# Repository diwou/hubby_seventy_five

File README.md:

# HUB75 NTP Flip Clock

Eine animierte Flip-Clock auf einem oder zwei 64×32 HUB75 LED-Matrix-Displays, betrieben von einem ESP32-S3.
Zeigt Uhrzeit (NTP-synchronisiert), Datum und aktuelle Wetterdaten an. Vollständig über ein Browser-Webinterface konfigurierbar — kein Neu-Flashen notwendig.

**Aktuelle Version:** 1.6.2

**Repository:** https://codeberg.org/diwou/hubby_seventy_five

**Lizenz:** CC BY-NC-SA 4.0, siehe [LICENSE](LICENSE)

**Browser-Installer:** `index.html` bzw. `install.html` nutzen automatisch `Firmware/latest/manifest.json`

<p>
  
</p>

---

## Inhalt

1. [Features](#features)
2. [Hardware](#hardware)
3. [Verkabelung / GPIO](#verkabelung--gpio)
4. [Software-Setup (PlatformIO)](#software-setup-platformio)
5. [Manuelles Update Ohne IDE](#manuelles-update-ohne-ide)
6. [Erstbetrieb](#erstbetrieb)
7. [Webinterface](#webinterface)
8. [Konfigurationsreferenz](#konfigurationsreferenz)
9. [Display-Layout](#display-layout)
10. [Animationsmodi](#animationsmodi)
11. [Sekundenanzeige-Modi](#sekundenanzeige-modi)
12. [REST-API](#rest-api)
13. [Architektur / Code-Struktur](#architektur--code-struktur)
14. [Changelog](#changelog)
15. [Lizenz](#lizenz)

---

## Features

- **Animierte Flip-Clock** — Ziffernwechsel mit Slide-Up- oder Cross-Dissolve-Animation
- **NTP-Zeitsynchronisation** — bis zu 3 konfigurierbare NTP-Server, automatischer Re-Sync
- **Wetteranzeige** — aktuelles Wetter + 3-Tage-Vorhersage via OpenWeatherMap API
- **Captive Portal** — bei fehlendem WLAN öffnet sich automatisch ein Konfigurations-Hotspot
- **Webinterface** — vollständige Konfiguration im Browser unter `http://hub75clock.local`
- **Umschaltbares Panel-Layout** — 1× HUB75 oder 2× HUB75 nebeneinander, mit vorbereiteter Mapping-Struktur für spätere 2×2-Layouts
- **OTA-Updates** — Firmware-Update über WLAN (ArduinoOTA)
- **Konfigurierbare Farben** — 8 Farbwähler für alle Display-Elemente
- **Mehrere Anzeigemodi** — 12h/24h, 4 Datumsformate, 4 Sekundenanzeige-Varianten
- **Zweisprachig** — Wochentage und Wetterbeschreibungen auf Deutsch oder Englisch
- **Double-Buffering** — kein Flackern oder Tearing

---

## Hardware

| Komponente | Beschreibung |
|---|---|
| **Mikrocontroller** | Freenove ESP32-S3 WROOM N16R8 (16 MB Flash, 8 MB PSRAM) |
| **Display** | 64×32 HUB75 RGB LED-Matrix, 1 oder 2 Panels nebeneinander |
| **Pegelwandler** | 74HCT245 (3,3 V → 5 V für HUB75-Signale) |

### KiCad / Platine

Die Platine liegt unter [`kicad/`](kicad/). Die bearbeitbaren KiCad-Quellen liegen in [`kicad/source/`](kicad/source/), die auslieferbaren Fertigungsdaten für Revision `0.3` in [`kicad/fab/rev0.3/`](kicad/fab/rev0.3/). Dort findest Du Gerber, Bohrdaten, BOM, Positionsdateien und das komplette Fertigungspaket als ZIP.

---

## Verkabelung / GPIO

Das HUB75-Panel wird über einen **74HCT245**-Pegelwandler angeschlossen (3,3 V ESP32 → 5 V HUB75).

| HUB75-Signal | GPIO |
|---|---|
| R1 | 4 |
| G1 | 5 |
| B1 | 6 |
| R2 | 7 |
| G2 | 8 |
| B2 | 9 |
| A | 10 |
| B | 11 |
| C | 12 |
| D | 13 |
| E | –1 (ungenutzt, 32-Zeilen-Panel) |
| CLK | 14 |
| LAT | 17 |
| OE | 18 |

> **Hinweis:** Pin E wird nur bei 64-Zeilen-Panels benötigt. Bei diesem 32-Zeilen-Panel bleibt er unverbunden (–1).

---

## Software-Setup (PlatformIO)

### Voraussetzungen

- [PlatformIO](https://platformio.org/) (CLI oder VSCode-Extension)
- USB-Kabel oder WLAN (für OTA nach Erstflash)

### Befehle

```bash
# Firmware bauen
pio run

# Firmware flashen (USB, /dev/ttyACM0)
pio run --target upload

# Firmware flashen (OTA, wenn schon eingerichtet)
# → upload_port in platformio.ini auf IP-Adresse setzen
pio run --target upload

# Serieller Monitor (115200 Baud)
pio device monitor

# Build-Verzeichnis leeren
pio run --target clean
```

Nach jedem erfolgreichen `pio run` exportiert PlatformIO die flashbaren Dateien automatisch nach:

```text
Firmware/<Version>/
Firmware/latest/
```

Dort liegen jeweils:
- `bootloader.bin`
- `partitions.bin`
- `boot_app0.bin`
- `firmware.bin`
- `manifest.json`

Damit hast Du pro Version direkt einen vorbereiteten Satz fuer Browser-Flasher oder Release-Downloads.

Fuer einen einfachen USB-Erstflash ohne IDE gibt es ausserdem die Dateien `index.html` und `install.html`.
`index.html` dient als Startseite fuer statisches Hosting wie Codeberg Pages und leitet auf den eigentlichen Installer weiter. `install.html` verwendet automatisch den neuesten Export aus `Firmware/latest/manifest.json`.

> **OTA vs. USB:** In `platformio.ini` ist standardmäßig OTA (`upload_protocol = espota`) konfiguriert.
> Für USB-Flash die Zeile `upload_protocol = espota` auskommentieren und `upload_port = /dev/ttyACM0` einkommentieren.

### Repository klonen

```bash
git clone ssh://git@codeberg.org/diwou/hubby_seventy_five.git
cd hubby_seventy_five
```

### Verwendete Bibliotheken

| Bibliothek | Version | Zweck |
|---|---|---|
| `mrfaptastic/ESP32 HUB75 LED MATRIX PANEL DMA Display` | ^3.0.14 | DMA-Display-Treiber |
| `adafruit/Adafruit GFX Library` | ^1.12.5 | Text, Formen, Farben |
| `mathieucarbou/ESPAsyncWebServer` | ^3.3.0 | Asynchroner Webserver |
| `mathieucarbou/AsyncTCP` | ^3.2.0 | Async-TCP-Unterbau |
| `bblanchon/ArduinoJson` | ^7.2.0 | JSON (Config + OWM-API) |

---

## Manuelles Update Ohne IDE

Wer weder die Arduino IDE noch VS Code mit PlatformIO nutzen moechte, kann die Dateien aus `Firmware/latest/` oder aus einer festen Version wie `Firmware/1.6.2/` direkt mit `esptool` flashen.

Die vier relevanten Flash-Offets sind:

```text
0x0000   bootloader.bin
0x8000   partitions.bin
0xE000   boot_app0.bin
0x10000  firmware.bin
```

Vorbereitung:
- Geraet per USB anschliessen
- Seriellen Port ermitteln
- Falls noetig `esptool` installieren: `pip install esptool`

### Linux

USB-Port haeufig: `/dev/ttyACM0` oder `/dev/ttyUSB0`

```bash
esptool.py --chip esp32s3 --port /dev/ttyACM0 --baud 921600 --before default_reset --after hard_reset write_flash -z \
  0x0000 Firmware/latest/bootloader.bin \
  0x8000 Firmware/latest/partitions.bin \
  0xE000 Firmware/latest/boot_app0.bin \
  0x10000 Firmware/latest/firmware.bin
```

### macOS

USB-Port haeufig: `/dev/cu.usbmodem...` oder `/dev/cu.usbserial...`

```bash
esptool.py --chip esp32s3 --port /dev/cu.usbmodemXXXX --baud 921600 --before default_reset --after hard_reset write_flash -z \
  0x0000 Firmware/latest/bootloader.bin \
  0x8000 Firmware/latest/partitions.bin \
  0xE000 Firmware/latest/boot_app0.bin \
  0x10000 Firmware/latest/firmware.bin
```

### Windows

USB-Port haeufig: `COM3`, `COM4`, `COM5`, ...

```powershell
esptool.py --chip esp32s3 --port COM4 --baud 921600 --before default_reset --after hard_reset write_flash -z `
  0x0000 Firmware/latest/bootloader.bin `
  0x8000 Firmware/latest/partitions.bin `
  0xE000 Firmware/latest/boot_app0.bin `
  0x10000 Firmware/latest/firmware.bin
```

Hinweise:
- Wenn `esptool.py` nicht gefunden wird, klappt oft auch `python -m esptool`.
- Bei einer festen Release-Version statt `Firmware/latest/` einfach z. B. `Firmware/1.6.2/` verwenden.
- Wer gar nichts lokal installieren moechte, kann alternativ weiter den Browser-Installer nutzen.
- Der Browser-Installer ist bereits auf dem aktuellen Stand: `Firmware/latest/manifest.json` zeigt derzeit auf Version `1.6.2`.

---

## Erstbetrieb

1. **Firmware flashen** (USB):
   ```bash
   # upload_port in platformio.ini auf /dev/ttyACM0 setzen
   pio run --target upload
   ```

2. **Mit dem Hotspot verbinden:**
   Das Display zeigt `AP-Modus` und den SSID-Namen `HUB75CLOCK-XXXX`.
   Mit diesem WLAN verbinden — das Captive Portal öffnet sich automatisch.
   (Falls nicht: Browser öffnen und `http://192.168.4.1` aufrufen.)

3. **WLAN konfigurieren:**
   Im Tab **WLAN** → SSID und Passwort eingeben → **Speichern & Neustart**.

4. **Nach dem Neustart:**
   Das Display scrollt kurz die IP-Adresse und `hub75clock.local`.
   Das Webinterface ist erreichbar unter:
   - `http://hub75clock.local` (mDNS, empfohlen)
   - `http://<IP-Adresse>` (IP aus dem Router ablesen oder Serial Monitor)

5. **OpenWeatherMap einrichten** (optional, für Wetteranzeige):
   - Kostenloser API-Key: [openweathermap.org](https://openweathermap.org/api)
   - Im Tab **Wetter** → API-Key + Stadtname eingeben → **Speichern**

6. **Zeitzone prüfen:**
   Im Tab **NTP** → Zeitzone als POSIX-String einstellen.
   Standard: `CET-1CEST,M3.5.0,M10.5.0/3` (Europa/Berlin mit Sommerzeit)

---

## Webinterface

Das Webinterface ist in sechs Tabs gegliedert:

Geschuetzte API-Aktionen verwenden HTTP Basic Auth. Standardzugang nach einem
Factory Reset: Benutzer `admin`, Passwort `hub75clock`. Das Web-Passwort sollte
im Tab **WLAN** geaendert werden.

### Status
Zeigt Systeminformationen in Echtzeit (Auto-Refresh jede Sekunde):
- Firmware-Version, IP-Adresse, WLAN-SSID und Signalstärke (RSSI)
- Uptime, aktuelle Uhrzeit
- NTP-Synchronisationsstatus und aktiver NTP-Server
- Wetter-Standort, aktuelle Temperatur und Wetterbedingung
- Nächste geplante NTP- und Wetter-Aktualisierung
- Freier Heap-Speicher

Schaltflächen: **Aktualisieren**, **Neustart**, **Factory Reset**

### WLAN
- SSID und Passwort für das Heimnetz
- AP-Passwort (leer = offener Hotspot ohne Passwort, sonst mindestens 8 Zeichen)
- Web-Passwort fuer HTTP Basic Auth (Benutzer `admin`, mindestens 8 Zeichen)
- WLAN-Verbindungs-Timeout (Standard: 30 s)

### NTP
- Bis zu 3 NTP-Server (Standard: `pool.ntp.org`, `time.google.com`, `time.cloudflare.com`)
- Sync-Intervall (Standard: 15 min)
- Zeitzone: Freitext-POSIX-String oder Auswahl aus Vorlagen (Berlin, London, Athen, UTC, USA)

### Wetter
- OpenWeatherMap API-Key
- Standort: Stadtname mit Geo-Suche **oder** GPS-Koordinaten (Breitengrad / Längengrad)
- Temperatureinheit: Celsius oder Fahrenheit
- Abruf-Intervall (Standard: 30 min)

### Anzeige
- Helligkeit (0–255)
- HUB75-Layout: `1x HUB75 (64x32)` oder `2x HUB75 nebeneinander (128x32)`
- Sprache: Deutsch / Englisch (Wochentage, Wetterbeschreibungen)
- Zeitformat: 24h oder 12h (AM/PM-Indikator)
- Datumsformat: 4 Varianten (siehe [Konfigurationsreferenz](#konfigurationsreferenz))
- Animations-Modus: Slide-Up oder Cross-Dissolve
- Sekundenanzeige: Bar / Wanderpunkt / Dots / HH:MM:SS
- Wetter-Wechselintervall (untere Zeile, Standard: 6 s)
- Scroll-Geschwindigkeit (30 = schnell, 200 = langsam, Standard: 80 ms/Pixel)
- **Farben:** 8 Farbwähler für alle Display-Elemente

Änderungen am HUB75-Layout werden erst nach einem Neustart aktiv, weil die Matrix-DMA-Konfiguration beim Booten initialisiert wird.

### OTA
- OTA-Updates aktivieren / deaktivieren
- Optionales OTA-Passwort
- OTA-Hostname: `hub75clock.local`, Port: 8266

---

## Konfigurationsreferenz

Alle Einstellungen werden in `/cfg.json` auf dem LittleFS-Dateisystem gespeichert.

### WLAN

| Parameter | Standard | Beschreibung |
|---|---|---|
| `sta_ssid` | `""` | SSID des Heimnetzwerks |
| `sta_pass` | `""` | WLAN-Passwort |
| `ap_password` | `""` | Passwort für den Konfigurationshotspot (leer = offen) |
| `web_password` | `hub75clock` | Passwort fuer das Webinterface, Benutzer `admin` |
| `wifi_timeout_sec` | `30` | Verbindungs-Timeout in Sekunden |

### NTP

| Parameter | Standard | Beschreibung |
|---|---|---|
| `ntp1` | `pool.ntp.org` | Primärer NTP-Server |
| `ntp2` | `time.google.com` | Sekundärer NTP-Server |
| `ntp3` | `time.cloudflare.com` | Tertiärer NTP-Server |
| `ntp_interval_min` | `15` | Re-Sync-Intervall in Minuten |
| `tz` | `CET-1CEST,M3.5.0,M10.5.0/3` | Zeitzone als POSIX-String |

**Zeitzone-Beispiele:**

| Zeitzone | POSIX-String |
|---|---|
| Europa/Berlin (mit Sommerzeit) | `CET-1CEST,M3.5.0,M10.5.0/3` |
| Europa/London | `GMT0BST,M3.5.0/1,M10.5.0` |
| UTC | `UTC0` |
| USA/New York | `EST5EDT,M3.2.0,M11.1.0` |
| USA/Los Angeles | `PST8PDT,M3.2.0,M11.1.0` |

### Wetter

| Parameter | Standard | Beschreibung |
|---|---|---|
| `owm_apikey` | `""` | OpenWeatherMap API-Key |
| `owm_city` | `""` | Stadtname (z. B. `Berlin`) |
| `owm_lat` / `owm_lon` | `0.0` | GPS-Koordinaten (nur wenn `owm_use_coords=true`) |
| `owm_use_coords` | `false` | `true` = Koordinaten, `false` = Stadtname |
| `owm_unit` | `0` | `0` = Celsius, `1` = Fahrenheit |
| `owm_interval_min` | `30` | Abruf-Intervall in Minuten |

### Anzeige

| Parameter | Standard | Beschreibung |
|---|---|---|
| `brightness` | `90` | Display-Helligkeit (0–255) |
| `lang` | `"de"` | Sprache: `"de"` oder `"en"` |
| `time_12h` | `0` | `0` = 24h, `1` = 12h (AM/PM) |
| `date_format` | `0` | Datumsformat (0–3, siehe unten) |
| `anim_mode` | `0` | `0` = Slide-Up, `1` = Cross-Dissolve |
| `seconds_mode` | `0` | `0` = Bar, `1` = Pulse, `2` = Dots, `3` = HH:MM:SS |
| `display_panel_cols` | `2` | Aktuell unterstützt: `1` = ein Panel, `2` = zwei Panels nebeneinander |
| `display_panel_rows` | `1` | Vorbereitung für späteres 2×2-Layout; derzeit im Webinterface fest auf `1` |
| `display_panel_map` | `0` | Vorbereitung für Mapping-Modi: `0` = linear, `1` = ZigZag/Serpentine; derzeit noch nicht im Webinterface auswählbar |
| `bottom_cycle_sec` | `6` | Wechselintervall der Wetterzeile in Sekunden |
| `scroll_speed_ms` | `40` | Scroll-Geschwindigkeit in ms pro Pixel (30–200) |

**Datumsformate:**

| Wert | Beispiel | Beschreibung |
|---|---|---|
| `0` | `Mo 17.03.26` | Wochentag + TT.MM.JJ (Standard) |
| `1` | `Mo 17.03` | Wochentag + TT.MM (ohne Jahr) |
| `2` | `17.03.2026` | TT.MM.JJJJ (lang, ohne Wochentag) |
| `3` | `03/17/26` | MM/TT/JJ (US-Format) |

### Farben

Alle Farben im Format `#RRGGBB`:

| Parameter | Standard | Element |
|---|---|---|
| `color_digit` | `#FFC832` | Uhrziffern (Gold/Amber) |
| `color_date` | `#64A0FF` | Datumtext (Blau) |
| `color_temp` | `#FF8C28` | Temperaturanzeige (Orange) |
| `color_warn` | `#FFDC00` | Wochentag / Warnmeldungen (Gelb) |
| `color_info` | `#A0A0A0` | Info-Texte (Grau) |
| `color_sec` | `#C88C14` | Sekunden-Balken (Dunkelamber) |
| `color_sec5` | `#00DC46` | 5s-Marke im Sekundenbalken (Grün) |
| `color_sec10` | `#50DCFF` | 10s-Marke im Sekundenbalken (Cyan) |

### OTA

| Parameter | Standard | Beschreibung |
|---|---|---|
| `ota_enabled` | `true` | OTA-Updates aktiviert |
| `ota_password` | `""` | OTA-Passwort (leer = kein Passwort) |

---

## Display-Layout

Die Firmware kann aktuell mit einem oder zwei 64×32-HUB75-Panels betrieben werden:

| Einstellung | Virtuelle Größe | Verhalten |
|---|---:|---|
| `1x HUB75` | 64×32 px | Uhr, Datum und Wetter laufen wie im klassischen Ein-Panel-Layout auf einem Panel |
| `2x HUB75 nebeneinander` | 128×32 px | Uhr bleibt links, Datum nutzt das rechte Panel, die Wetterzeile scrollt über die volle Breite |

Die Konfiguration speichert bereits `display_panel_cols`, `display_panel_rows` und `display_panel_map`. Dadurch ist die Struktur für ein späteres 2×2-Layout vorbereitet. Für 2×2 muss zusätzlich das physische Panel-Mapping implementiert werden, z. B. linear oder ZigZag/Serpentine passend zur Verkabelung.

Bei `1x HUB75` verwendet `HH:MM:SS` bewusst das kompakte Ein-Panel-Layout aus Version `1.5.4`, damit die sechs Ziffern auf 64×32 px nicht zu groß dargestellt werden. Bei `2x HUB75 nebeneinander` bleibt das größere aktuelle Layout aktiv.

Das 64×32-Basislayout ist in vier Bereiche aufgeteilt:

```
┌─────────────────────────────────────────────────────────────────┐ y=0
│                                                                 │
│   Uhrzeit: HH:MM (10×14px Bitmap-Ziffern, Gold/Amber)          │ y=0..13
│                                                                 │
├─────────────────────────────────────────────────────────────────┤ y=14
│   Sekundenanzeige (2px, Mode 0–2) — entfällt bei Mode 3        │ y=14..15
├─────────────────────────────────────────────────────────────────┤ y=16
│   Gap (1px)                                                     │ y=16
├─────────────────────────────────────────────────────────────────┤ y=17
│   Datum: z. B. "Mo 17.03.26"  /  Temperatur (rechtsbündig)     │ y=17..23
├─────────────────────────────────────────────────────────────────┤ y=24
│   Gap (1px)                                                     │ y=24
├─────────────────────────────────────────────────────────────────┤ y=25
│   Wetter (rotierend): Aktuell → Di-Forecast → Mi → Do          │ y=25..31
└─────────────────────────────────────────────────────────────────┘ y=31
```

### Ziffern-Positionen HH:MM (Mode 0–2)

```
H1=7  H2=19  [:]=31  M1=35  M2=47
```
(Kolon: 2×2-Pixel-Punkte bei y=3 und y=9)

### Ziffern-Positionen HH:MM:SS (Mode 3)

```
H1=2  H2=11  [C1]=20..21  M1=23  M2=32  [C2]=41..42  S1=44  S2=53
```
(9px-Ziffern, 2×2-Pixel-Kolons)

### Wetterzeile (rotierend, Wechsel alle `bottom_cycle_sec` Sekunden)

| Modus | Inhalt | Beispiel |
|---|---|---|
| 0 | Aktuelles Wetter scrollend | `+12.4C  Leicht bew.` |
| 1 | Vorhersage +1 Tag statisch | `Di +15/-3` |
| 2 | Vorhersage +2 Tage statisch | `Mi +12/-1` |
| 3 | Vorhersage +3 Tage statisch | `Do +8/-5` |

---

## Animationsmodi

### Slide-Up (`anim_mode = 0`)
- 14 Frames à 15 ms = ~210 ms Gesamtdauer
- Phase 1 (Frame 0–6): Alte Ziffer gleitet nach oben aus dem Slot heraus
- Phase 2 (Frame 7–13): Neue Ziffer gleitet von unten in den Slot hinein

### Cross-Dissolve (`anim_mode = 1`)
- 14 Frames à 18 ms = ~252 ms Gesamtdauer
- Phase 1 (Frame 0–6): Alte Ziffer blendet von voll → schwarz aus (7 Helligkeitsstufen)
- Phase 2 (Frame 7–13): Neue Ziffer blendet von schwarz → voll ein

### Kolon-Animation
- Synchron zum Sekundenwechsel: Cross-Dissolve-Puls (14 Frames à 18 ms)
- Der Kolon bleibt dauerhaft hell und pulsiert kurz zum Sekundenwechsel
- Außerhalb der Animation: statisch in Ziffernfarbe

---

## Sekundenanzeige-Modi

| Modus | Beschreibung |
|---|---|
| `0` — Bar | Balken füllt sich von links; 5s-Marken grün, 10s-Marken cyan |
| `1` — Pulse | Ein Leuchtpunkt wandert mit kurzem Schweif von links nach rechts |
| `2` — Dots | 60 Einzelpunkte; vergangene Sekunden leuchten, zukünftige sind gedimmt |
| `3` — HH:MM:SS | Kein Sekundenbalken — Sekunden erscheinen direkt in der Uhrzeitzeile |

---

## REST-API

Das Webinterface kommuniziert über eine interne JSON-API. Alle Endpunkte sind unter der IP-Adresse des Geräts erreichbar und per HTTP Basic Auth geschützt (`admin` + Web-Passwort).

| Methode | Endpunkt | Beschreibung |
|---|---|---|
| `GET` | `/api/config` | Konfigurationswerte als JSON abrufen; gespeicherte Passwoerter/API-Keys werden nicht ausgeliefert |
| `POST` | `/api/config` | Konfiguration aktualisieren (JSON-Body) |
| `GET` | `/api/status` | Systemstatus (Firmware, IP, WLAN, NTP, Wetter) |
| `GET` | `/api/geocode?q={Stadt}` | Ortsuche via OWM Geocoding API (bis zu 5 Treffer) |
| `GET` | `/api/restart` | Gerät neu starten |
| `GET` | `/api/reset` | Factory Reset (alle Einstellungen löschen + Neustart) |

### Beispiel: Konfiguration per curl ändern

```bash
# Helligkeit auf 150 setzen
curl -X POST http://hub75clock.local/api/config \
  -u admin:<web-passwort> \
  -H "Content-Type: application/json" \
  -d '{"brightness": 150}'

# Auf ein einzelnes HUB75-Panel umstellen; Neustart danach erforderlich
curl -X POST http://hub75clock.local/api/config \
  -u admin:<web-passwort> \
  -H "Content-Type: application/json" \
  -d '{"display_panel_cols": 1, "display_panel_rows": 1}'

# Aktuellen Status abrufen
curl -u admin:<web-passwort> http://hub75clock.local/api/status
```

---

## Architektur / Code-Struktur

```
src/
├── main.cpp       — Setup, Loop, WiFi-State-Machine, NTP-Sync, Wetter-Timer
├── config.h       — Config-Struct, LittleFS-Persistenz (configLoad/Save/Reset)
├── display.h      — HUB75-Initialisierung, Bitmap-Font, Flip-Animationen, Display-Update
├── weather.h      — OpenWeatherMap HTTP-Fetch, Wetter-Datenstruktur, Geocoding
└── webserver.h    — AsyncWebServer, REST-API, Captive-Portal, OTA-Setup, HTML/CSS/JS
include/
├── config.h       — `APP_VERSION_BASE` als sichtbare Basisversion
└── version_generated.h — beim Build erzeugter Firmware-String mit Git-Hash
```

### Wichtige Abhängigkeiten

```
main.cpp
  ├── config.h      (cfg, configLoad/Save/Reset)
  ├── display.h     (displayInit, displayUpdate, displayReset, ...)
  │     └── weather.h (WeatherData, forecastDayName)
  └── webserver.h   (webServerSetup, otaSetup, dnsServer)
        ├── extern MatrixPanel_I2S_DMA* dma_display  ← aus display.h
        └── extern bool ntpSynced                    ← aus main.cpp
```

> Alle `.h`-Dateien definieren globale Variablen direkt (kein ODR-Problem, da nur eine `.cpp`-Datei kompiliert wird).

### WiFi-State-Machine (`main.cpp`)

```
Start
  │
  ▼
wifiConnect() ──── Erfolg ──→ mDNS + NTP-Sync + WebServer + OTA + Wetter
  │
  Timeout
  │
  ▼
startAP() ──→ Hotspot "HUB75CLOCK-XXXX" + Captive-Portal + WebServer
                   (kein NTP, kein Wetter im AP-Modus)

Loop:
  WiFi verloren? ──→ alle 30 s Reconnect-Versuch
```

### Double-Buffering / Kein Flackern

Die HUB75-Bibliothek verwendet zwei DMA-Buffer. Jeder Frame wird in den Back-Buffer gezeichnet, dann mit `flipDMABuffer()` atomisch sichtbar gemacht. Statische Ziffern werden **nicht** gelöscht und neu gezeichnet — nur animierende oder als `dirty` markierte Slots werden aktualisiert.

Nach `ESP.restart()` werden RAM-Überreste durch `displayReset()` in `setup()` explizit gelöscht (verhindert Ghosting beim Soft-Reboot).

### Bitmap-Font

Die Ziffern basieren auf dem **Dottie 8×8-Font**, konvertiert in 10×14-Pixel-Bitmaps (PROGMEM). Jede Ziffer besteht aus 14 `uint16_t`-Werten (eine pro Zeile), wobei Bit 9 die linkeste Spalte repräsentiert.

---

## Changelog

Die vollständige Änderungshistorie steht in [CHANGELOG.md](CHANGELOG.md).

## Lizenz

Dieses Projekt steht unter der Lizenz **Creative Commons Attribution-NonCommercial-ShareAlike 4.0 International**.

Kurzform:
- Namensnennung erforderlich
- Keine kommerzielle Nutzung
- Bearbeitungen müssen unter derselben Lizenz weitergegeben werden

Details siehe [LICENSE](LICENSE) und:
https://creativecommons.org/licenses/by-nc-sa/4.0/

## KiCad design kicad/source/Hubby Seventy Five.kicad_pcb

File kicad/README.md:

# KiCad Hardware

Dieses Verzeichnis enthält die Platinenquellen und die exportierten Fertigungsdaten für den HUB75 Flip Clock.

## Struktur

- `source/` - bearbeitbare KiCad-Quellen für Revision `0.3`
- `fab/rev0.3/gerber/` - Gerber-, Bohr- und Layer-Exporte
- `fab/rev0.3/bom/` - BOM, Designatoren, Positionen und Netlist
- `fab/rev0.3/Hubby_Seventy_Five_0.3.zip` - komplettes Fertigungspaket für den Bestelldienstleister

## Kurz-BOM

_Abgeleitet aus `fab/rev0.3/bom/bom.csv` und per `scripts/render_kicad_bom_summary.py` generiert. Falls sich die Platine ändert, die Übersicht mit `python3 scripts/render_kicad_bom_summary.py --write-readme` neu schreiben._

<!-- BOM_SUMMARY_START -->

| Bereich | Bauteile | Bauform | Menge | Zweck |
|---|---|---|---:|---|
| MCU | `U5` ESP32-S3-WROOM-1 | ESP32-S3-WROOM-1 | 1 | Hauptprozessor, WLAN, Steuerlogik und PSRAM |
| Takt / Sensorik | `U2` DS3231S, `U4` BME680, `U21` VEML7700-TT | Bosch_LGA-8_3x3mm_P0.8mm_ClockwisePinNumbering, SOIC-16W_7.5x10.3mm_P1.27mm, XDCR_VEML7700-TT | 3 | Echtzeituhr, Temperatur/Luftfeuchte/Luftdruck, Helligkeit |
| Pegelwandler | `U3/U6` 74HCT245 | TSSOP-20_4.4x6.5mm_P0.65mm | 2 | 3,3 V auf 5 V fuer HUB75-Signale |
| Spannungsversorgung | `BT1` CR2032, `D1` SS14, `U1` TLV76133DCY | BatteryHolder_MYOUNG_BS-07-A1BJ001_CR2032, D_SMA, SOT-223-3_TabPin2 | 3 | 3,3-V-Regler, Schutzdiode, Backup-Batterie |
| Anschlüsse | `J1` USB_C_Receptacle_USB2.0_16P, `J2` PWR IN, `J3` HUB75 Connector | IDC-Header_2x08_P2.54mm_Vertical, JST_VH_B4P-VH_1x04_P3.96mm_Vertical, USB_C_Receptacle_GCT_USB4105-xx-A_16P_TopMnt_Horizontal | 3 | Strom, USB, Display-Anschluss |
| Taster | `SW1` Reset, `SW2` Factory Reset, `SW3` Boot | SW_PUSH_6mm | 3 | Bedienung und Flash-Modus |
| Widerstände | `R1/R2` 5k1, `R3/R4/R5` 4k7, `R7` 1k, `R6/R8/R9/R10/R11` 10k, `R27` 10 | 0805 | 12 | Pullups, LED-/Signalbegrenzung, Schutz |
| Kondensatoren | `C1/C2/C3/C4/C7/C9/C10/C11/C13/C28` 100n, `C12` 1µ, `C5/C6/C8/C27` 10µ | 0805 | 15 | Abblockung und Pufferung |
| Anzeige / Status | `D2` PWR | 0805 | 1 | Power-LED |

<!-- BOM_SUMMARY_END -->

Hinweise:
- `H1` bis `H4` sind Montagebohrungen und tauchen deshalb nicht in der BOM-CSV auf.
- Die vollständige, exportierte Stückliste liegt zusätzlich als CSV unter `fab/rev0.3/bom/`.
- `U5` muss ein ESP32-S3-WROOM-1 mit PSRAM sein; das Projekt nutzt die PSRAM-Variante des Moduls.

## Hinweise

- Lokale KiCad-Backups bleiben per `.gitignore` ausgeschlossen.
- Die exportierten Fertigungsdaten sind bewusst im Repo, damit man sie ohne KiCad direkt bestellen oder prüfen kann.

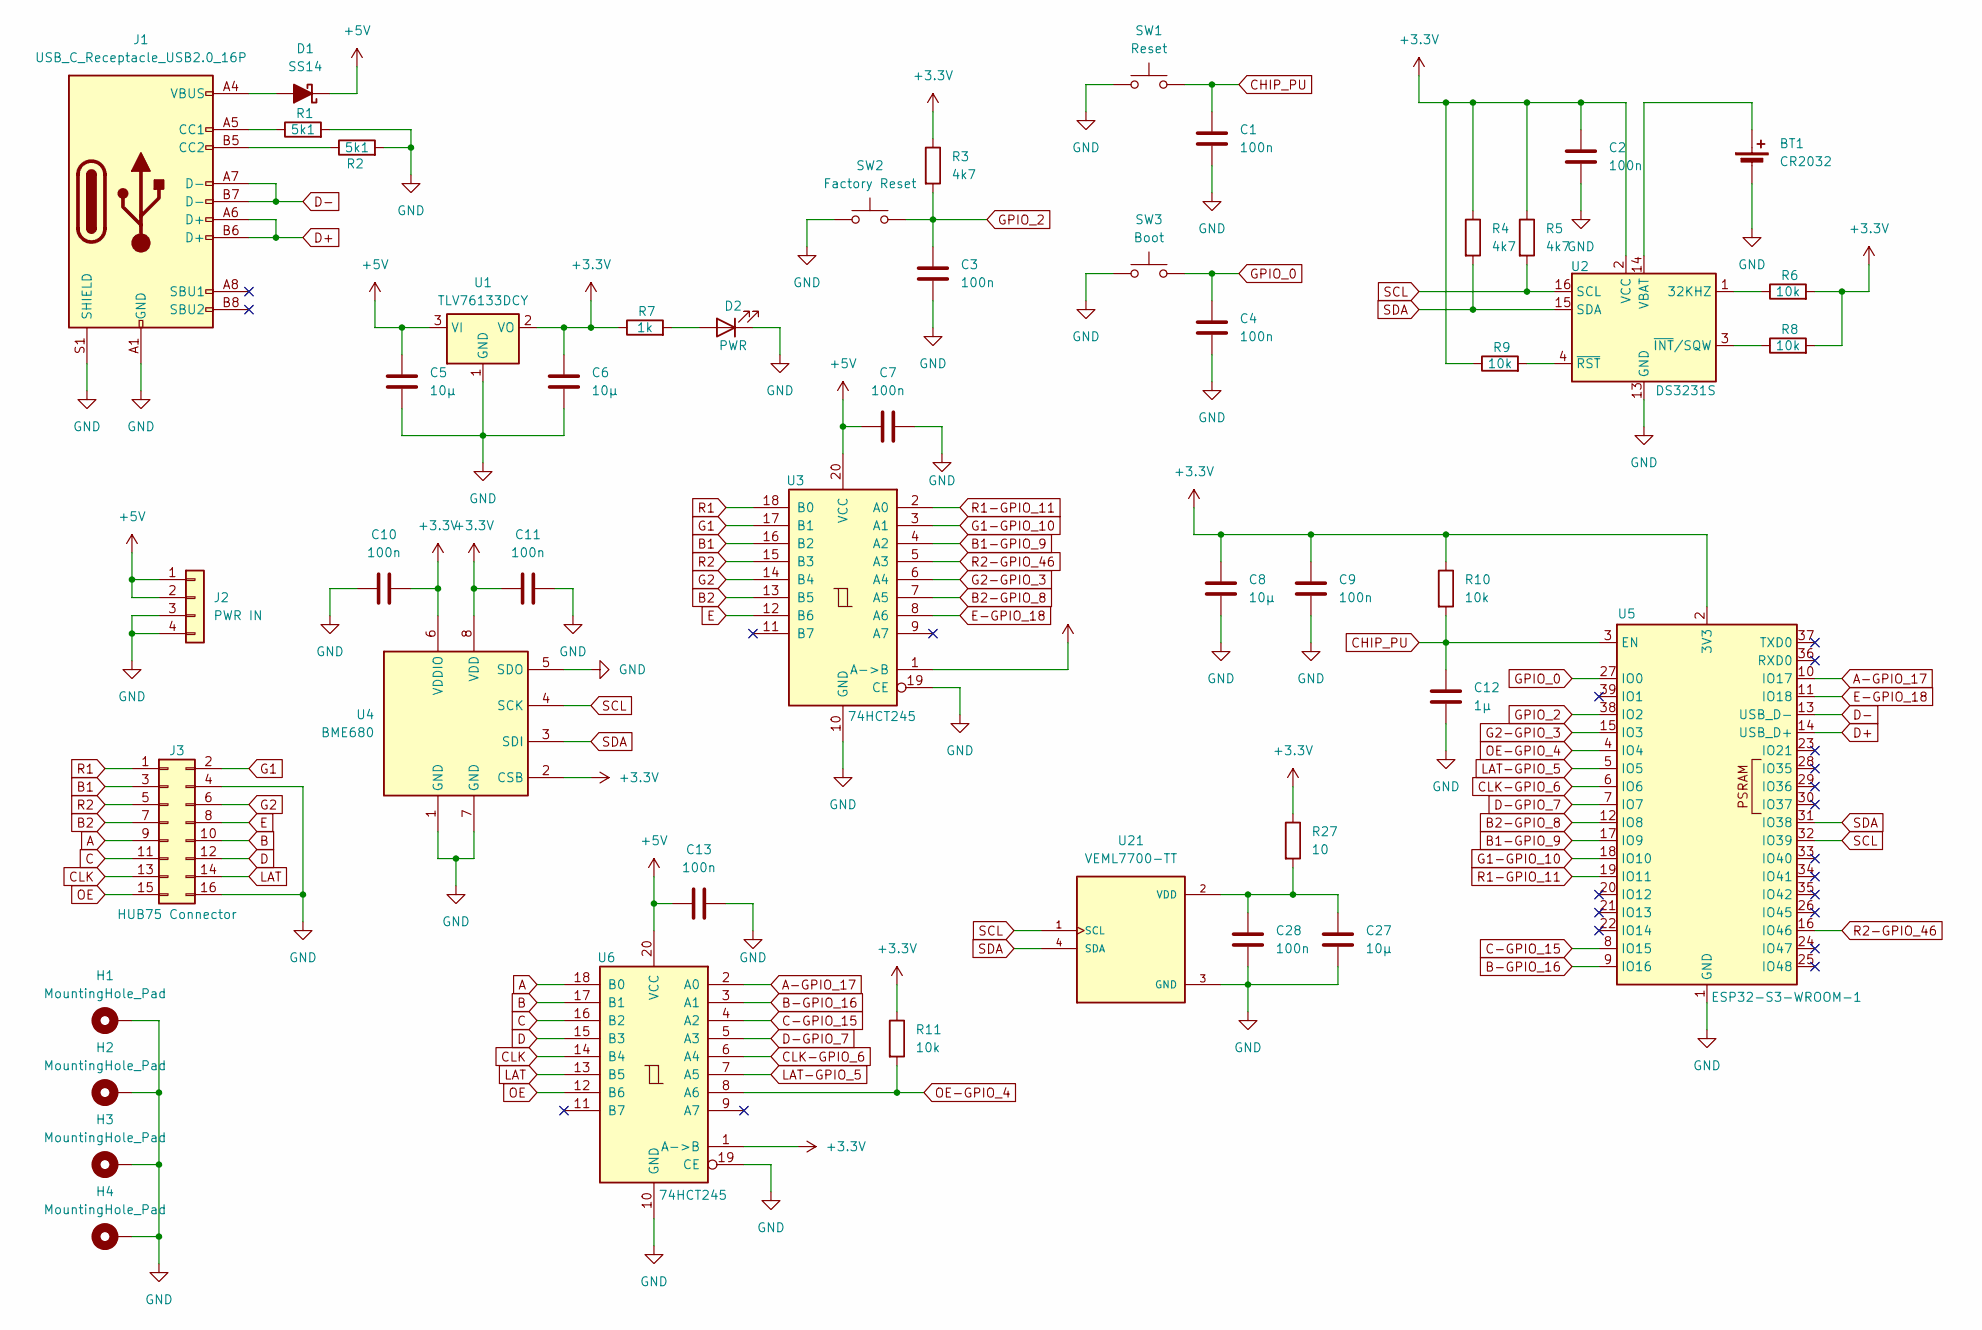
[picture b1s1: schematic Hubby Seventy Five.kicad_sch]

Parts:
BT1: CR2032; BatteryHolder_MYOUNG_BS-07-A1BJ001_CR2032
C1, C2, C3, C4, C7, C9, C10, C11, C13, C28: 100n; C_0805_2012Metric_Pad1.18x1.45mm_HandSolder
C5, C6, C8, C27: 10µ; C_0805_2012Metric_Pad1.18x1.45mm_HandSolder
C12: 1µ; C_0805_2012Metric_Pad1.18x1.45mm_HandSolder
D1: SS14; D_SMA
D2: PWR; LED_0805_2012Metric_Pad1.15x1.40mm_HandSolder
H1, H2, H3, H4: MountingHole_Pad; MountingHole_3.2mm_M3_DIN965_Pad
J1: USB_C_Receptacle_USB2.0_16P; USB_C_Receptacle_GCT_USB4105-xx-A_16P_TopMnt_Horizontal
J2: PWR IN; JST_VH_B4P-VH_1x04_P3.96mm_Vertical
J3: HUB75 Connector; IDC-Header_2x08_P2.54mm_Vertical
R1, R2: 5k1; R_0805_2012Metric_Pad1.20x1.40mm_HandSolder
R3, R4, R5: 4k7; R_0805_2012Metric_Pad1.20x1.40mm_HandSolder
R6, R8, R9, R10, R11: 10k; R_0805_2012Metric_Pad1.20x1.40mm_HandSolder
R7: 1k; R_0805_2012Metric_Pad1.20x1.40mm_HandSolder
R27: 10; R_0805_2012Metric_Pad1.20x1.40mm_HandSolder
SW1: Reset; SW_PUSH_6mm
SW2: Factory Reset; SW_PUSH_6mm
SW3: Boot; SW_PUSH_6mm
U1: TLV76133DCY; SOT-223-3_TabPin2
U2: DS3231S; SOIC-16W_7.5x10.3mm_P1.27mm
U3, U6: 74HCT245; TSSOP-20_4.4x6.5mm_P0.65mm
U4: BME680; Bosch_LGA-8_3x3mm_P0.8mm_ClockwisePinNumbering
U5: ESP32-S3-WROOM-1
U21: VEML7700-TT; XDCR_VEML7700-TT; PARTREV 1.6

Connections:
+3.3V: C2.1, C6.1, C8.1, C9.1, C10.2, C11.1, R3.1, R4.1, R5.1, R6.2, R7.1, R8.2, R9.1, R10.1, R11.1, R27.1, U1.2 (VO), U2.2 (VCC), U3.1 (A->B), U4.2 (CSB), U4.6 (VDDIO), U4.8 (VDD), U5.2 (3V3), U6.1 (A->B)
+5V: C5.1, C7.1, C13.1, D1.1 (K), J2.1, J2.2, U1.3 (VI), U3.20 (VCC), U6.20 (VCC)
A: J3.9, U6.18 (B0)
A-GPIO_17: U5.10 (IO17), U6.2 (A0)
B: J3.10, U6.17 (B1)
B1: J3.3, U3.16 (B2)
B1-GPIO_9: U3.4 (A2), U5.17 (IO9)
B2: J3.7, U3.13 (B5)
B2-GPIO_8: U3.7 (A5), U5.12 (IO8)
B-GPIO_16: U5.9 (IO16), U6.3 (A1)
C: J3.11, U6.16 (B2)
C-GPIO_15: U5.8 (IO15), U6.4 (A2)
CHIP_PU: C1.1, C12.1, R10.2, SW1.2, U5.3 (EN)
CLK: J3.13, U6.14 (B4)
CLK-GPIO_6: U5.6 (IO6), U6.6 (A4)
D: J3.12, U6.15 (B3)
D+: J1.A6 (D+), J1.B6 (D+), U5.14 (USB_D+)
D-: J1.A7 (D-), J1.B7 (D-), U5.13 (USB_D-)
D-GPIO_7: U5.7 (IO7), U6.5 (A3)
E: J3.8, U3.12 (B6)
E-GPIO_18: U3.8 (A6), U5.11 (IO18)
G1: J3.2, U3.17 (B1)
G1-GPIO_10: U3.3 (A1), U5.18 (IO10)
G2: J3.6, U3.14 (B4)
G2-GPIO_3: U3.6 (A4), U5.15 (IO3)
GND: BT1.2 (-), C1.2, C2.2, C3.2, C4.2, C5.2, C6.2, C7.2, C8.2, C9.2, C10.1, C11.2, C12.2, C13.2, C27.2, C28.2, D2.1 (K), H1.1, H2.1, H3.1, H4.1, J1.A1 (GND), J1.A12 (GND), J1.B1 (GND), J1.B12 (GND), J1.S1 (SHIELD), J2.3, J2.4, J3.4, J3.16, R1.2, R2.2, SW1.1, SW2.1, SW3.1, U1.1 (GND), U2.5 (GND), U2.6 (GND), U2.7 (GND), U2.8 (GND), U2.9 (GND), U2.10 (GND), U2.11 (GND), U2.12 (GND), U2.13 (GND), U3.10 (GND), U3.19 (CE), U4.1 (GND), U4.5 (SDO), U4.7 (GND), U5.1 (GND), U5.40 (GND), U5.41 (GND), U6.10 (GND), U6.19 (CE), U21.3 (GND)
GPIO_0: C4.1, SW3.2, U5.27 (IO0)
GPIO_2: C3.1, R3.2, SW2.2, U5.38 (IO2)
LAT: J3.14, U6.13 (B5)
LAT-GPIO_5: U5.5 (IO5), U6.7 (A5)
unnamed: BT1.1 (+), U2.14 (VBAT)
unnamed: D1.2 (A), J1.A4 (VBUS), J1.A9 (VBUS), J1.B4 (VBUS), J1.B9 (VBUS)
unnamed: D2.2 (A), R7.2
unnamed: J1.A5 (CC1), R1.1
unnamed: J1.B5 (CC2), R2.1
unnamed: R6.1, U2.1 (32KHZ)
unnamed: R8.1, U2.3 (~INT/SQW)
unnamed: R9.2, U2.4 (~RST)
unnamed: C27.1, C28.1, R27.2, U21.2 (VDD)
OE: J3.15, U6.12 (B6)
OE-GPIO_4: R11.2, U5.4 (IO4), U6.8 (A6)
R1: J3.1, U3.18 (B0)
R1-GPIO_11: U3.2 (A0), U5.19 (IO11)
R2: J3.5, U3.15 (B3)
R2-GPIO_46: U3.5 (A3), U5.16 (IO46)
SCL: R5.2, U2.16 (SCL), U4.4 (SCK), U5.32 (IO39), U21.1 (SCL)
SDA: R4.2, U2.15 (SDA), U4.3 (SDI), U5.31 (IO38), U21.4 (SDA)

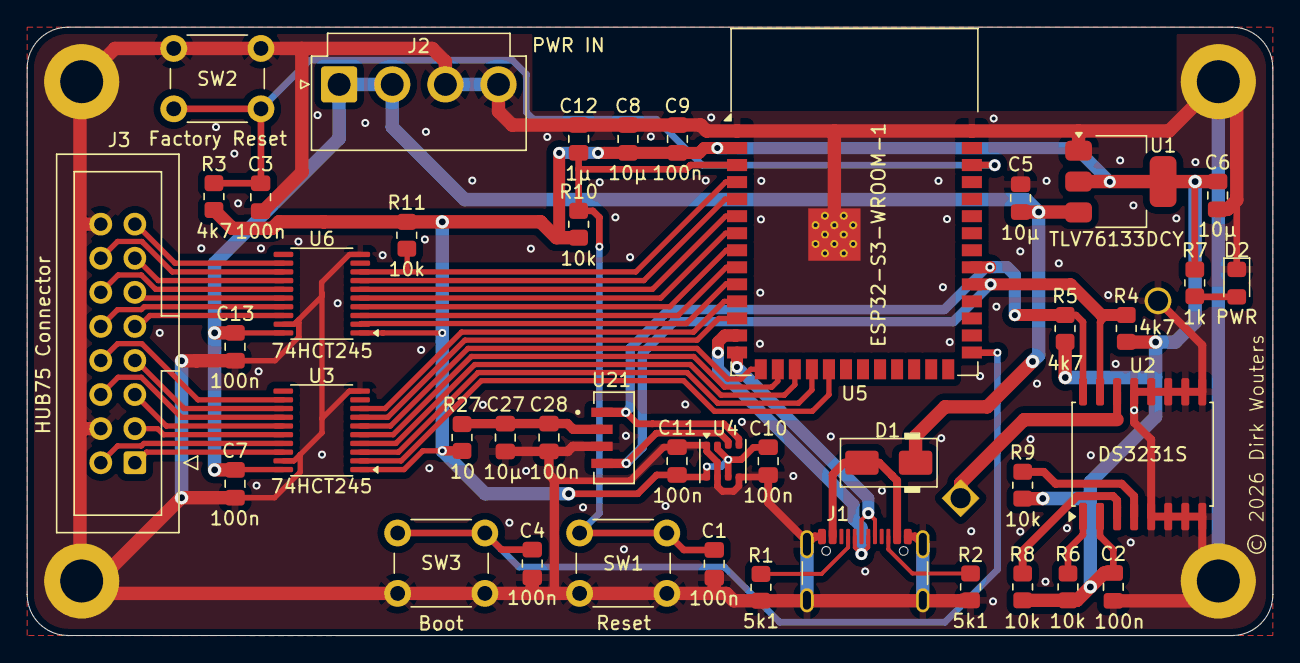
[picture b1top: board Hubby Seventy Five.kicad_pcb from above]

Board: 2 copper layers, 92.8 x 45.3 mm, 47 parts (1 on the bottom side), 47 nets.

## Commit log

2026-04-06 Initial public release v1.5.4
2026-04-06 Prepare installer page and firmware export
2026-04-06 Publish installer site
2026-04-06 Add index page for Codeberg Pages root
2026-04-06 Add index page for site root
2026-04-06 Trigger Codeberg Pages deploy
2026-04-06 Trigger Pages after making repo public
2026-04-06 Add installer button to README
2026-04-06 Sync README update to pages
2026-04-06 Keep firmware exports out of main branch
2026-04-06 Remove local-only helper scripts
2026-04-10 feat: expand dual-panel clock layout
2026-04-10 docs: record changelog codeberg reference
2026-04-10 fix: refine forecast spacing and enlarge clock
2026-04-10 docs: update changelog commit reference
2026-04-10 fix: use taller hhmm clock glyphs
2026-04-10 docs: reference codeberg ids per changelog entry
2026-04-10 fix: replace ineffective clock scaling with tall hhmm renderer
2026-04-10 docs: update changelog clock reference
2026-04-10 fix: enlarge hhmmss and clear mode switch artifacts
2026-04-10 docs: update changelog clock references
2026-04-10 fix: switch clock digits to bitmap-style scaling
2026-04-10 docs: update changelog font reference
2026-04-10 fix: finalize hhmmss layout and ota display lock
2026-04-10 docs: finalize changelog references for 1.6.0
2026-04-10 docs: record release id for 1.6.0
2026-04-10 docs: add manual update instructions without ide
2026-04-10 docs: note web ui firmware update for next version
2026-04-10 docs: finalize next-version changelog reference
2026-04-10 feat: add firmware upload via web interface
2026-04-10 docs: finalize changelog reference for web update
2026-04-10 fix: rebalance hhmmss colon spacing
2026-04-10 docs: finalize hhmmss colon changelog reference
2026-04-11 Add configurable HUB75 panel layout
2026-04-11 Prepare release 1.6.1
2026-04-11 chore: add reproducible cspell tooling
2026-04-11 docs: finalize cspell changelog reference
2026-04-19 Fix brief display blanks
2026-04-19 Add Codeberg reference to changelog
2026-04-19 Animate forecast transitions
2026-04-19 Document forecast transition animation
2026-04-19 Document forecast transition compile fix
2026-04-19 Fix forecast transition clipping
2026-04-19 Document forecast transition fix
2026-04-19 Keep forecast transition in weather area
2026-04-19 Document forecast transition adjustment
2026-04-19 Restore weather cycle transitions
2026-04-19 Document weather cycle restoration
2026-04-19 Restore weather cycle loop and clip transitions
2026-04-19 Document weather loop clipping fix
2026-04-19 Separate forecast fade phases
2026-04-19 Document separated forecast fade phases
2026-04-19 Keep forecast transitions out of clock area
2026-04-19 Document forecast clock area fix
2026-04-19 Redraw clock during forecast transition
2026-04-19 Document clock redraw during forecast transition
2026-04-19 Restore clock after forecast transition
2026-04-19 Add forecast transition clock restore reference
2026-04-19 Clip forecast transitions to weather area
2026-04-19 Document forecast clipping fix
2026-04-19 Publish 1.6.2 firmware
2026-04-19 Add watchdog and cspell updates
2026-04-19 Replace task WDT with heartbeat monitor
2026-04-19 Add KiCad source and fabrication exports
2026-04-19 Move KiCad fab zip to revision root
2026-04-19 Add human-readable KiCad BOM summary
2026-04-19 Fix watchdog and regenerate KiCad BOM summary
2026-04-19 Expose watchdog state in web UI
2026-04-19 Avoid blocking weather fetch during startup
2026-04-19 Reset WiFi stack on boot
2026-04-19 Unify firmware version source
2026-04-19 Reduce weather line flicker
2026-04-19 Soften weather scroll motion
2026-04-19 Smooth current weather scroll
2026-04-19 Stabilize weather scroll timing
2026-04-19 Load weather earlier and smooth scroll start
2026-04-19 Document weather startup refs
2026-04-19 Remove scroll overlay blending
2026-04-19 Document scroll overlay fix
2026-04-19 Reset weather scroll after forecast
2026-04-19 Document forecast scroll reset
2026-04-19 Smooth weather scrolling with supersampling
2026-04-19 Document supersampled weather scroll
2026-04-19 Avoid full weather band redraw
2026-04-19 Document reduced weather redraw flicker
2026-04-19 Batch weather band redraws by scanline
2026-04-19 Document scanline weather batching
2026-04-19 Enable PSRAM double buffering
2026-04-19 Document PSRAM double buffering
2026-04-19 Revert PSRAM double buffering
2026-04-19 Document PSRAM buffer rollback
2026-04-19 Revert weather scroll experiments
2026-04-19 Document weather rollback
2026-04-19 Smooth current weather scroll with supersampling
2026-04-19 Document smoother current weather scroll
2026-04-19 Try smoother weather scroll with fixed-point timing
2026-04-19 Reset weather scroll timing on restart
2026-04-19 Smooth current weather with 2x intermediate buffer
2026-04-19 Revert broken current weather 2x scroll experiment
2026-04-19 Reset weather scroll after forecast transition
2026-04-23 Document KiCad release workflow
2026-04-24 fix: HH:MM:SS auf 7px verbreitert
2026-04-24 docs: Changelog um Referenz ergänzt
2026-04-24 docs: Changelog-Reihenfolge korrigiert
2026-04-24 fix: HH:MM:SS im Legacy-Pfad verbreitert
2026-04-24 docs: Changelog auf Legacy-Fix referenziert
2026-04-24 fix: HH:MM:SS-Kantenbreite ohne Lochverlust
2026-04-24 docs: Changelog auf Loch-freien Fix referenziert
2026-04-24 fix: HH:MM:SS-Kantenform verfeinert
2026-04-24 docs: Changelog mit Kanten-Fix referenziert
2026-04-24 fix: HH:MM:SS mit eigenem 7px-Font
2026-04-24 docs: Changelog mit 7px-Font referenziert
2026-04-24 fix: HH:MM:SS auf volle Hoehe zurueck
2026-04-24 docs: Changelog auf volle Hoehe referenziert
2026-04-24 fix: HH:MM:SS-Font mit 2px-Strichen
2026-04-24 docs: Changelog mit 2px-Font referenziert
2026-04-24 revert: Font-Experimente zurücknehmen
2026-04-24 revert: heutige Font-Änderungen zurücknehmen
2026-04-24 fix: HH:MM:SS-Font auf 7x14-Tabelle umstellen
2026-04-24 docs: Changelog für HH:MM:SS-Font ergänzen
2026-04-24 fix: HH:MM:SS-Abstaende nach den Doppelpunkten korrigieren
2026-04-24 docs: Changelog fuer HH:MM:SS-Abstaende ergaenzen
2026-04-24 fix: OWM-Wetterpfad absichern
2026-04-24 docs: OWM-Fix im Changelog vermerken
2026-04-24 fix: HH:MM:SS-Ziffer 6 korrigieren
2026-04-24 docs: Changelog fuer Ziffer-6-Korrektur ergaenzen
2026-04-26 fix: sichere Web-API und Versionsquelle
2026-04-26 docs: Review-Fixes dokumentieren
2026-04-27 fix: Wetterabruf beim Boot entkoppeln
2026-04-27 docs: Boot-Fix im Changelog dokumentieren
2026-04-28 PlatformIO stabilisieren
2026-04-28 fix: stabilisiere Wetter-Scroll-Zeitbasis
2026-04-28 fix: glaette Wetter-Scroll per Subpixel-Blending
2026-04-28 fix: entferne unscharfes Wetter-Scroll-Blending
2026-04-28 fix: entlaste OTA und beschleunige Wetter-Scroll
2026-04-30 fix: stabilize cold boot startup
2026-05-11 feat: DS3231-Zeitquelle und RTC-Webfunktionen integrieren
2026-05-11 docs: Changelog-Referenzen auf Commit-ID aktualisieren
2026-05-11 feat: erweitere RTC/VEML status und kompakte 1x-forecast darstellung
2026-05-11 docs: aktualisiere changelog referenzen fuer rtc-veml und forecast-fix
2026-05-11 fix: stabilisiere autohelligkeit und strukturiere status-tabs
2026-05-11 docs: aktualisiere changelog-referenzen fuer autohelligkeit-fix
2026-05-11 feat: integriere bme680 wetterdaten und passe 1x-forecast spacing an
2026-05-11 docs: aktualisiere changelog-referenzen fuer bme680 und forecast-spacing
2026-05-11 fix: entkopple bme680 messung vom render-loop
2026-05-11 docs: aktualisiere changelog-referenz fuer bme680 async-fix
2026-05-11 fix: stoppe bme680 polling waehrend wetter-wait und setze 2px spacing
2026-05-11 docs: aktualisiere changelog-referenzen fuer wetter-wait-fix
2026-05-11 fix: justiere forecast-abstaende fuer 1x display
2026-05-11 docs: aktualisiere changelog-referenz fuer forecast-feintuning
2026-05-11 fix: aktualisiere statusdaten ajax-weit in allen tabs
2026-05-11 docs: aktualisiere changelog-referenz fuer ajax-refresh-fix
2026-05-11 fix: deaktiviere bme680 heater fuer stabile umgebungstemperatur
2026-05-11 docs: aktualisiere changelog-referenz fuer bme680-heater-fix
2026-05-11 docs: behebe markdownlint-regeln im changelog
2026-05-11 fix: erzwinge bme680 update alle 2 sekunden
2026-05-11 docs: aktualisiere changelog-referenz fuer bme680-2s-update
2026-05-11 fix: korrigiere bme680 async ready-zeitpunkt
2026-05-11 fix: verbessere bme680 reaktionsverhalten und lesefallback
2026-05-11 docs: aktualisiere changelog-referenz fuer bme680-reaktionsfix
2026-05-12 fix(ntp): Sync-Intervall und TZ-Handling robust machen
2026-05-12 docs(changelog): Commit-Referenz fuer NTP-Fix nachziehen
2026-05-12 fix(time): RTC als UTC fuehren und echten NTP-Resync ausfuehren
2026-05-12 docs(changelog): Referenz fuer RTC/NTP-Fix nachziehen
2026-05-12 fix(time): DS3231-Stundenformat robust lesen und NTP als Live-Zeitquelle nutzen
2026-05-12 fix(time): DS3231-UTC-Dekodierung auf Dottie-Stand angleichen
2026-05-12 docs(changelog): Referenzen fuer Dottie-Zeitfix nachziehen
2026-05-12 fix(time): NTP-Syncpfad aus Dottie per UDP-Probe uebernehmen
2026-05-12 docs(changelog): Referenzen fuer Dottie-NTP-Portierung nachziehen
2026-05-12 fix(ntp): Sync-Intervall auf min=1 umstellen
2026-05-12 docs(changelog): Referenz fuer min-1 NTP-Intervall nachziehen
2026-05-13 fix(display): sichtbaren Slide-Up beim Ziffernwechsel wiederherstellen
2026-05-13 docs(changelog): Referenz fuer Slide-Up-Fix nachziehen

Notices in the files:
kicad/source/Hubby Seventy Five.kicad_pcb:
© 2026 Dirk Wouters
License: CC BY-NC-SA 4.0
